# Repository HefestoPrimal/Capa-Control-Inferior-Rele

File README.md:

# Activador Inferior para Relé

Esta PCB esta diseñada para soldarse directamente a la parte inferior de un relevador y manejarlo directamente con un microcontrolador a través de 2 pines de alimentación y uno de control, sumándole también 3 pines de salida correspondiente al COMUN, NORMALMENTE ABIERTO y NORMALMENTE CERRADO.
Su principal ventaja es el espacio utilizado y el hecho de contar con todos los componentes para una fase de potencia que proteja al microcontrolador de corrientes parásitas generadas por el mismo relevador.

### Circuito esquemático

### Vista en 3D

<table>
    <tr>
        <td style="border-collapse: collapse; border:none;">
	    
	</td>
	<td style="border-collapse: collapse; border: none;">
	    
	</td>
    </tr>
</table>

### Dimensiones

## Redes
- [Portafolio](https://github.com/HefestoPrimal/Portafolio)
- [Linkedin](https://www.linkedin.com/in/angel-diaz-mexatronica/)
- [YouTube](https://youtube.com/@mexatronica99)
- [Facebook](https://www.facebook.com/mexatronica99)
- [Instagram](https://www.instagram.com/mexatronica99/)
- [Pinterest](https://mx.pinterest.com/mexatronica99/)
- [TikTok](https://www.tiktok.com/@mexatronica99)

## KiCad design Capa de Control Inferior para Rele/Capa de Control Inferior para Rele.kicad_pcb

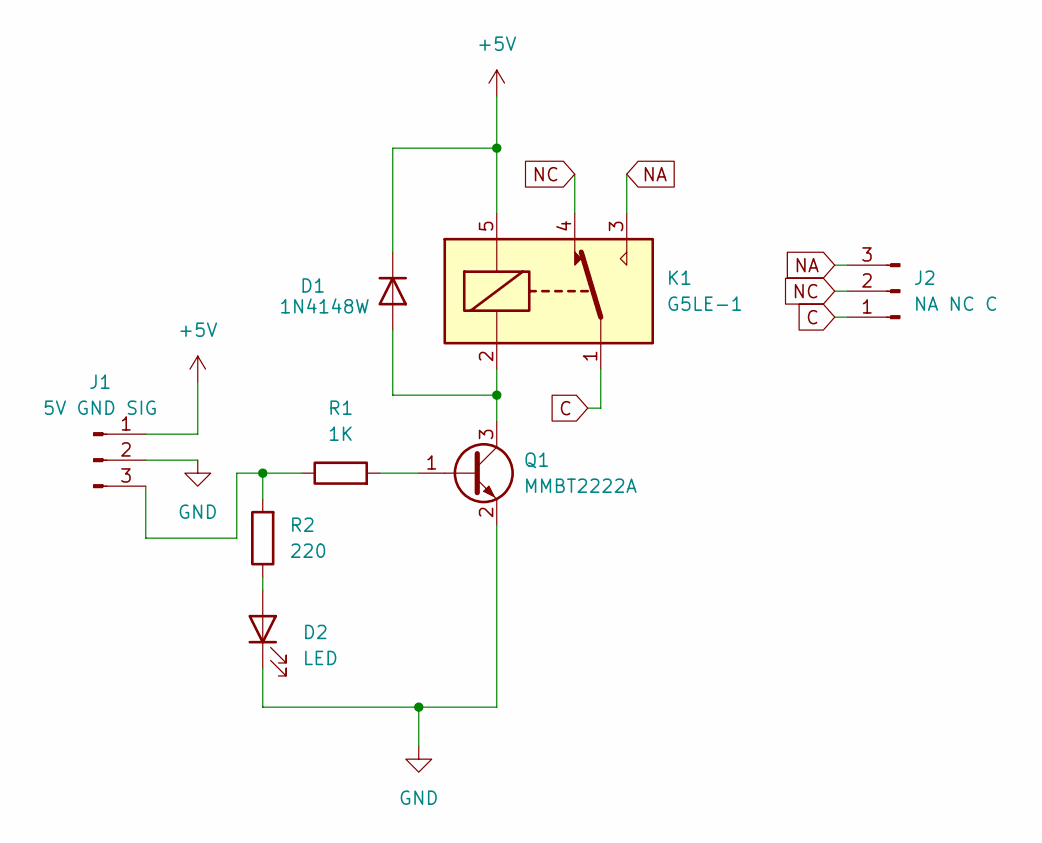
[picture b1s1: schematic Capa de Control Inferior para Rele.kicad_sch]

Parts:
D1: 1N4148W; D_SOD-123
D2: LED; LED_0402_1005Metric
J1: 5V GND SIG; PinSocket_1x03_P2.54mm_Vertical
J2: NA NC C; PinSocket_1x03_P2.54mm_Vertical
K1: G5LE-1; Relay_SPDT_Omron-G5LE-1
Q1: MMBT2222A; SOT-23
R1: 1K; R_0402_1005Metric
R2: 220; R_0402_1005Metric

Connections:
+5V: D1.1 (K), J1.1, K1.5
C: J2.1, K1.1
GND: D2.1 (K), J1.2, Q1.2 (E)
NA: J2.3, K1.3
NC: J2.2, K1.4
unnamed: D1.2 (A), K1.2, Q1.3 (C)
unnamed: D2.2 (A), R2.1
unnamed: J1.3, R1.1, R2.2
unnamed: Q1.1 (B), R1.2

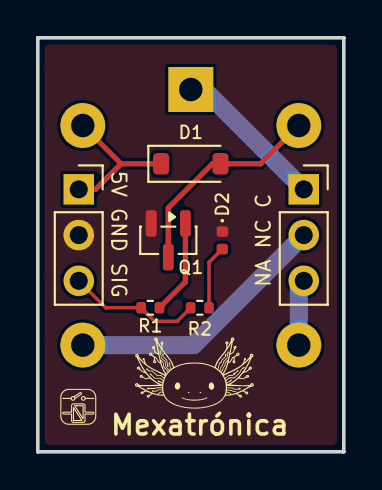
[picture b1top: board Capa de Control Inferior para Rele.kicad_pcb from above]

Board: 2 copper layers, 17.0 x 23.0 mm, 9 parts (1 on the bottom side), 9 nets.

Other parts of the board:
Mexatrónica: LOGO; Logo Mexatronica Huella 07mm

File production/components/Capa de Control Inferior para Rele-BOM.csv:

"Reference","Qty","Value","DNP","Exclude from BOM","Exclude from Board","Footprint","Datasheet"
"D1","1","1N4148W","","","","Diode_SMD:D_SOD-123","https://www.vishay.com/docs/85748/1n4148w.pdf"
"D2","1","LED","","","","LED_SMD:LED_0402_1005Metric",""
"J1","1","5V GND SIG","","","","Connector_PinSocket_2.54mm:PinSocket_1x03_P2.54mm_Vertical",""
"J2","1","NA NC C","","","","Connector_PinSocket_2.54mm:PinSocket_1x03_P2.54mm_Vertical",""
"K1","1","G5LE-1","","","","Relay_THT:Relay_SPDT_Omron-G5LE-1","http://www.omron.com/ecb/products/pdf/en-g5le.pdf"
"Q1","1","MMBT2222A","","","","Package_TO_SOT_SMD:SOT-23","https://assets.nexperia.com/documents/data-sheet/MMBT2222A.pdf"
"R1","1","1K","","","","Resistor_SMD:R_0402_1005Metric",""
"R2","1","220","","","","Resistor_SMD:R_0402_1005Metric",""

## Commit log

2026-04-21 Primer prototipo funcional para mandar a producir, ya adaptado para colocarlo por debajo del rele
2026-04-21 Agregar README con descripción e imagenes de referencia del proyecto, como renders, archivo esquemático y la vista de la PCB en KiCad
2026-04-22 Mejorar como se muestran las imagenes en el README
2026-04-22 Actualizar README.md
    Agregar extensión a imagen de muestra y cambiar la escala en la que se muestran algunas imágenes
2026-04-22 Actualizar README.md
    Cambiar escala en la que se muestra la imagen principal y agregar enlaces a redes sociales
2026-04-22 Agregar los archivos comprimidos para ordenar la placa en formato gerber comprimido junto con los archivos BOM y POS en formato CSV exportados desde KiCad
